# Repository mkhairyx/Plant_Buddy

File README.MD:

# Plant Buddy

## The reason I made it
I have a plant at a remote location and I only go there once in a while, I was afraid that that plant might die because of the lack of water so I decided to make this device. It work by connecting a water pump to it, then it drives this pump every 20 days by default (configurable in the code). It measures the soil humidity for feedback to the user (which is delivered through SMS).

## The poster

## Photos

|Schematic                                            |PCB                                    |3D View                                  |Showcase                                            |
|-----------------------------------------------------|---------------------------------------|-----------------------------------------|----------------------------------------------------|
|||||

## Step files
All of the step files can be found [here](./Step_Files/).
<br>

## Firmware
### Compile and flash using the Arduino IDE
If you want to edit the code, compile it yourself, then flash it; you can download the arduino sketch [here](./Source/Firmware/Arduino/plant_buddy).

### Flash the firmware as is
If you want to flash the firmware as is, you can download it [here](./source/Firmware/Firmware). <br>
You can use [ESPWebTool](https://esptool.spacehuhn.com) to flash the firmware directly to the ESP32 using your browser.<br>
Note that there might be some changes between the Arduino code and the firmware as some changes were made.

## Device Operation
### Power supply
The device is powered a 3.7V recharge Li-Po battery.<br>
The battery is recharged daily using a 3W 6V mini solar panel connected to a mini solar charger which is connected to a buck converter to operate the ESP32.<br>
The ESP32 goes into Deep Sleep mode in between watering sessions to help decrease energy consumption.<br>

### Startup Notification

Whenever the ESP32 wakes up, it sends a status report to the user containing:

* Current battery level
* Current soil moisture level
* Watering interval
* Reason for waking up

Example:

```
The device just booted up!
Battery level: 87%
Soil humidity: 42%
Watering interval: 3 days

Boot reason: Watering cycle completed successfully.
Watering again in 3 days.
```

Possible boot reasons:

| Boot Reason              | Description                                                                       |
| ------------------------ | --------------------------------------------------------------------------------- |
| Unknown Fault            | The device restarted unexpectedly due to an unknown error.                        |
| Watering Cycle Completed | A watering cycle has just finished successfully, and a new countdown has started. |
| First Boot               | The device has been powered on for the first time.                                |

## BOM
### BOM Table (components only)
|Name                                                 |Link                                   |Cost per one (EGP)                       |Cost per one (USD)                                  |Amount     |Total cost|
|-----------------------------------------------------|---------------------------------------|-----------------------------------------|----------------------------------------------------|-----------|----------|
|JST Connectors                                       |https://www.ram-e-shop.com/shop/pw-m-pcb-2pin-pw-m-2-pin-polarized-male-jst-xh2-54-connector-for-pcb-6463| EGP 0.60                                | $0.012                                             |5          | $0.060   |
|4.7uF Caps (1206)                                    |https://lampatronics.com/product/smd-multilayer-ceramic-capacitor-1206-4-7uf-16v-1pcs| EGP 1.50                                | $0.030                                             |4          | $0.120   |
|100nF Caps (0805)                                    |https://lampatronics.com/product/smd-multilayer-ceramic-capacitor-0805-2012-104-100nf-50v-1pcs-2| EGP 1.00                                | $0.020                                             |6          | $0.120   |
|1uF Caps (0805)                                      |https://lampatronics.com/product/smd-ceramic-capacitor-0805-1051uf-50v-1pcs| EGP 1.50                                | $0.030                                             |1          | $0.030   |
|10uF Caps (0805)                                     |https://lampatronics.com/product/smd-multilayer-ceramic-capacitor-0805-10610uf-16v-1pcs| EGP 1.50                                | $0.030                                             |1          | $0.030   |
|1N4148WS Diode                                       |https://lampatronics.com/product/smd-diode-1n4148ws-10pcs| EGP 7.50                                | $0.150                                             |1          | $0.150   |
|Screw terminal                                       |https://www.ram-e-shop.com/shop/r-3-roseta-2pin-2-pin-pcb-screw-terminal-block-pitch-5mm-r-3-5854| EGP 3.00                                | $0.060                                             |1          | $0.060   |
|Male headers                                         |https://store.fut-electronics.com/products/male-pin-headers-standard-2-54-mm-40-pin?_pos=1&_sid=73894fcce&_ss=r| EGP 10.00                               | $0.200                                             |1          | $0.200   |
|Female headers                                       |https://www.ram-e-shop.com/shop/ph35-1x4-female-ph35-pin-header-female-1x4-straight-2-54mm-6976| EGP 1.50                                | $0.030                                             |2          | $0.060   |
|AO3401 (transistor for pump)                         |https://uge-one.com/product/ao3401-sot23-general-purpose-p-channel-mosfet-smd-transistor-sot-23/| EGP 3.00                                | $0.060                                             |1          | $0.060   |
|1K ohm Resistors                                     |https://lampatronics.com/product/smd-resistor-1kohm-102-0805-10pcs| EGP 2.00                                | $0.040                                             |1          | $0.040   |
|1M ohm Resistors                                     |https://lampatronics.com/product/smd-resistor-1mohm-105-0805-10pcs| EGP 2.00                                | $0.040                                             |1          | $0.040   |
|10K ohm Resistors                                    |https://lampatronics.com/product/smd-resistor-10kohm-103-0805-10pcs| EGP 2.00                                | $0.040                                             |1          | $0.040   |
|330 ohm Resistors                                    |https://lampatronics.com/product/smd-resistor-330ohm-331-0805-10pcs| EGP 2.00                                | $0.040                                             |1          | $0.040   |
|1.5Kohm Resistors                                    |https://lampatronics.com/product/resistor-1-5k-ohm-1-4w-4pcs-2| EGP 0.30                                | $0.006                                             |1          | $0.006   |
|2K ohm Resistors                                     |https://lampatronics.com/product/smd-resistor-2kohm-202-0805-10pcs| EGP 2.00                                | $0.040                                             |1          | $0.040   |
|3K ohm Resistors                                     |https://lampatronics.com/product/smd-resistor-3kohm-302-0805-10pcs| EGP 2.00                                | $0.040                                             |1          | $0.040   |
|220 ohm Resistors                                    |https://lampatronics.com/product/smd-resistor-220ohm-221-0805-10pcs| EGP 2.00                                | $0.040                                             |1          | $0.040   |
|Reset Push Button                                    |https://lampatronics.com/product/push-button-4pin-long-6x6x13mm| EGP 1.50                                | $0.030                                             |1          | $0.030   |
|Voltage Regulator                                    |https://lampatronics.com/product/ams1117-33v-sot-223-33v-linear-voltage-regulator| EGP 2.00                                | $0.040                                             |1          | $0.040   |
|TLC555xD (Capacitive soil readings)                  |https://uge-one.com/product/tlc555cdr-low-power-cmos-timer-ic-smd-sop8/| EGP 35.00                               | $0.700                                             |1          | $0.700   |
|PC817 optocoupler                                    |https://lampatronics.com/product/pc817-optocoupler-dip-4| EGP 1.25                                | $0.025                                             |1          | $0.025   |
|ESP32 DevKit                                         |https://lampatronics.com/product/esp32-30pin-development-board-wifi-and-bluetooth| EGP 325.00                              | $6.500                                             |1          | $6.500   |
|Water Pump                                           |https://www.ram-e-shop.com/shop/dc-pump-6vdc-water-pump-3-6vdc-mini-120l-h-7422| EGP 45.00                               | $0.900                                             |1          | $0.900   |
|Hose (inner d: 6mm , outer d: 8mm) 1 Meter           |https://lampatronics.com/product/flexible-clear-hose-tube-pipe-6mm-airwater-pump-pvc| EGP 15.00                               | $0.300                                             |2          | $0.600   |
|Water Flow sensor                                    |https://store.fut-electronics.com/products/water-flow-rate-sensor?_pos=8&_sid=5e9c09df8&_ss=r| EGP 260.00                              | $5.200                                             |1          | $5.200   |
|SIM800L GSM Module                                   |https://store.fut-electronics.com/collections/gsm-gprs/products/sim800l-gprs-gsm-module-esp-core-board-with-built-in-antenna| EGP 280.00                              | $5.600                                             |1          | $5.600   |
|3W 6V Mini Solar Panel                               |https://store.fut-electronics.com/products/solar-cell-129-x-129-mm-3w?_pos=3&_sid=fdb2b11fe&_ss=r| EGP 155.00                              | $3.100                                             |1          | $3.100   |
|Mini solar charger                                   |https://store.fut-electronics.com/products/solar-usb-charger-for-lithium-batteries-lipo-rider?_pos=5&_sid=fdb2b11fe&_ss=r| EGP 160.00                              | $3.200                                             |1          | $3.200   |
|Battery                                              |https://store.fut-electronics.com/products/3-7v-rechargeable-polymer-lithium-ion-battery-ecocell?_pos=3&_sid=4fcef8d7d&_ss=r| EGP 125.00                              | $2.500                                             |1          | $2.500   |
|M5 Screws                                            |https://store.fut-electronics.com/products/screw-m5x25mm-hexagonal-head?_pos=5&_sid=c4191184f&_ss=r| EGP 2.00                                | $0.040                                             |4          | $0.160   |
|                                                     |                                       |                                         |                                                    |           |          |
|                                                     |                                       |                                         |                                                    |Whole Total| $29.731  |

### Quotes
[JLCPCB](https://jlcpcb.com) : $57.12

<br>
Note that local manufacturers might have different prices.

## Notes
A future V2 is planned with support for multiple probes, improved power efficiency, and user-requested status updates.

> Made and designed by [@mkhairyx](https://github.com/mkhairyx).<br>
Supported by [Fallout](https://fallout.hackclub.com/) and [Hack Club](https://hackclub.com).<br>

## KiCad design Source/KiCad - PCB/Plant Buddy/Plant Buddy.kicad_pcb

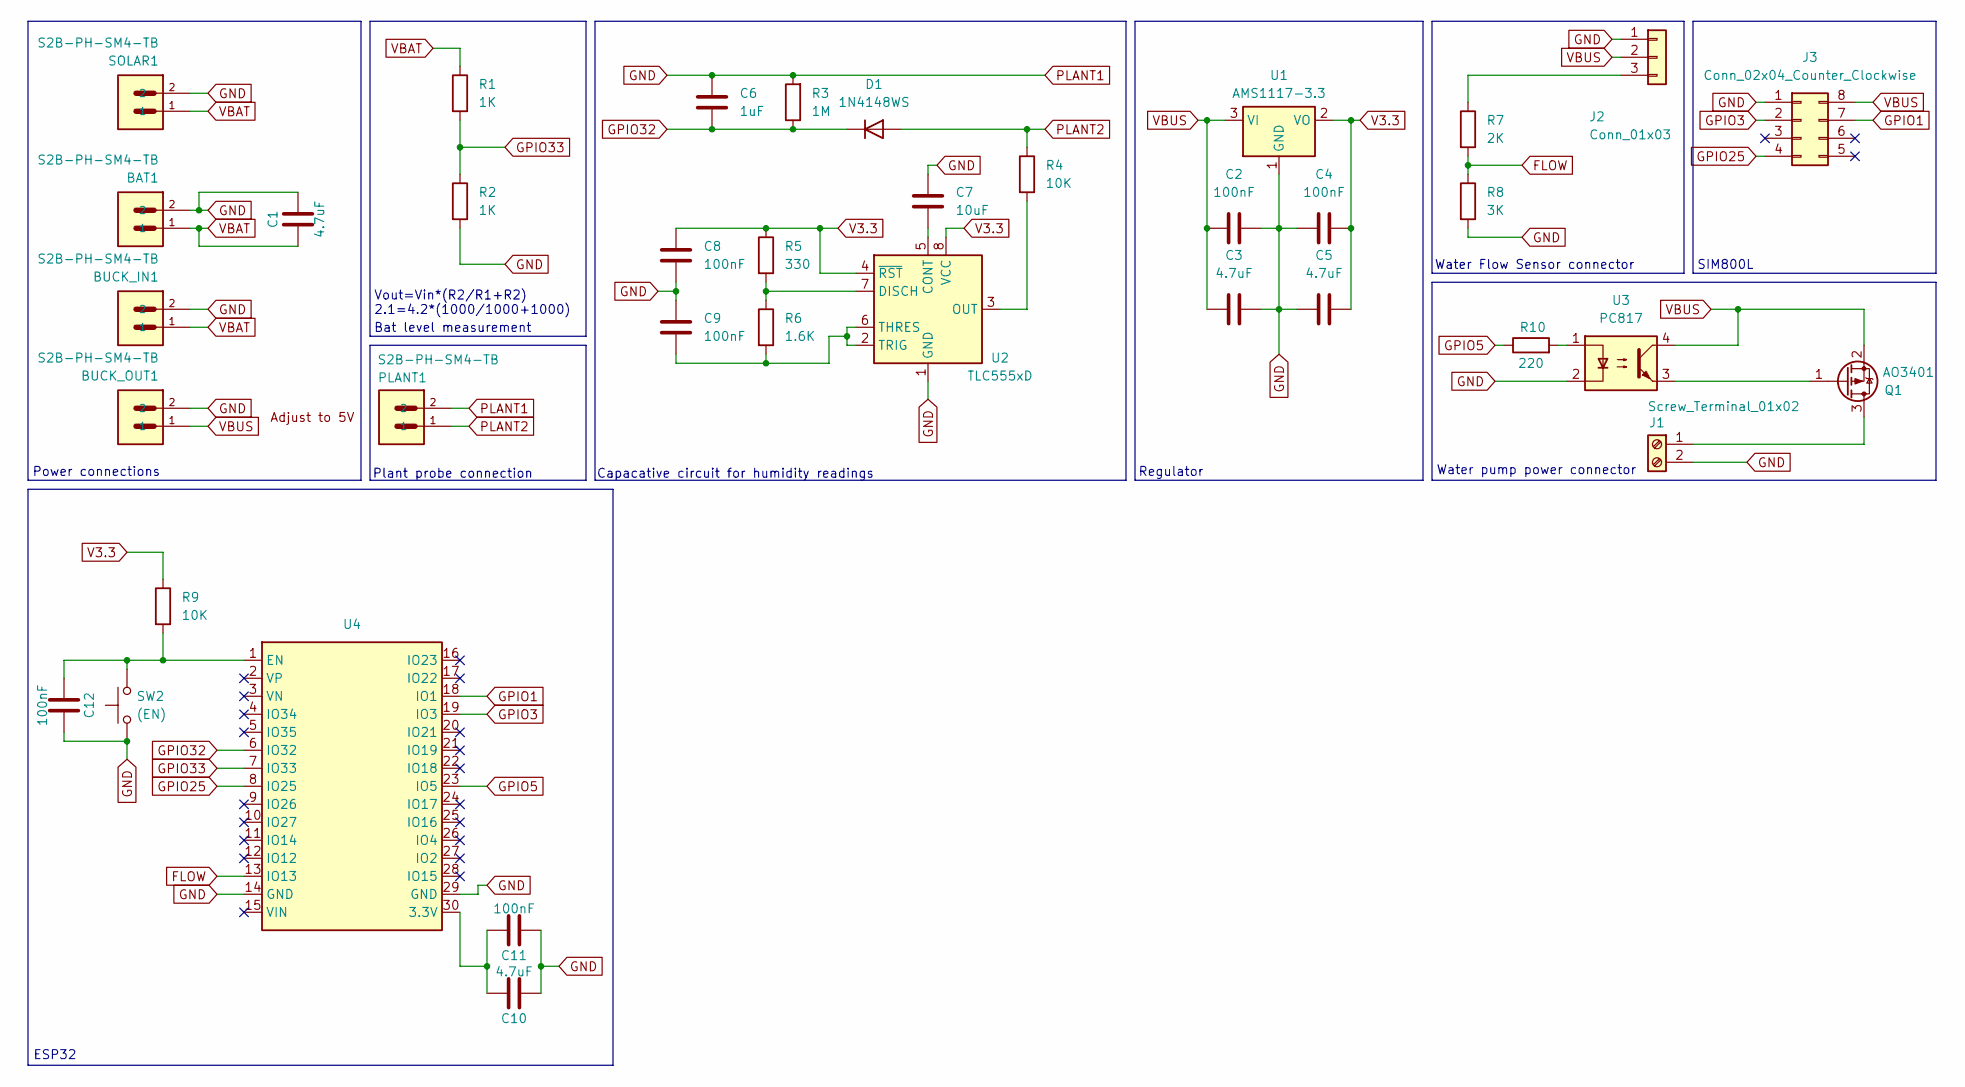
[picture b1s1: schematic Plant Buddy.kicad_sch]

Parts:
BAT1: S2B-PH-SM4-TB; JST_EH_B2B-EH-A_1x02_P2.50mm_Vertical
BUCK_IN1: S2B-PH-SM4-TB; JST_EH_B2B-EH-A_1x02_P2.50mm_Vertical
BUCK_OUT1: S2B-PH-SM4-TB; JST_EH_B2B-EH-A_1x02_P2.50mm_Vertical
C1, C3, C5, C10: 4.7uF; C_1206_3216Metric_Pad1.33x1.80mm_HandSolder
C2, C4, C8, C9: 100nF; C_0805_2012Metric_Pad1.18x1.45mm_HandSolder
C6: 1uF; C_0805_2012Metric_Pad1.18x1.45mm_HandSolder
C7: 10uF; C_0805_2012Metric_Pad1.18x1.45mm_HandSolder
C11, C12: 100nF; C_1206_3216Metric_Pad1.33x1.80mm_HandSolder
D1: 1N4148WS; D_SOD-323_HandSoldering
J1: Screw_Terminal_01x02; Altech_AK100_1x02_P5.00mm
J2: Conn_01x03; PinSocket_1x03_P2.54mm_Vertical
J3: Conn_02x04_Counter_Clockwise; PinSocket_2x04_P2.54mm_Vertical
PLANT1: S2B-PH-SM4-TB; JST_EH_B2B-EH-A_1x02_P2.50mm_Vertical
Q1: AO3401; SOT-23
R1, R2: 1K; R_0805_2012Metric_Pad1.20x1.40mm_HandSolder
R3: 1M; R_0805_2012Metric_Pad1.20x1.40mm_HandSolder
R4, R9: 10K; R_0805_2012Metric_Pad1.20x1.40mm_HandSolder
R5: 330; R_0805_2012Metric_Pad1.20x1.40mm_HandSolder
R6: 1.6K; R_Axial_DIN0207_L6.3mm_D2.5mm_P7.62mm_Horizontal
R7: 2K; R_0805_2012Metric_Pad1.20x1.40mm_HandSolder
R8: 3K; R_0805_2012Metric_Pad1.20x1.40mm_HandSolder
R10: 220; R_0805_2012Metric_Pad1.20x1.40mm_HandSolder
SOLAR1: S2B-PH-SM4-TB; JST_EH_B2B-EH-A_1x02_P2.50mm_Vertical
SW2: (EN); SW_PUSH_6mm_H13mm
U1: AMS1117-3.3; SOT-223-3_TabPin2
U2: TLC555xD; SOP-8_3.76x4.96mm_P1.27mm
U3: PC817; DIP-4_W7.62mm
U4: ESP32 DevKit

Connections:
FLOW: R7.2, R8.1, U4.13 (IO13)
GND: BAT1.2, BUCK_IN1.2, BUCK_OUT1.2, C1.2, C2.2, C3.2, C4.2, C5.1, C6.2, C7.1, C8.1, C9.1, C10.1, C11.1, C12.2, J1.2, J2.1, J3.1, PLANT1.2, R2.2, R3.2, R8.2, SOLAR1.2, SW2.1, U1.1 (GND), U2.1 (GND), U3.2, U4.14 (GND), U4.29 (GND)
GPIO1: J3.7, U4.18 (IO1)
GPIO3: J3.2, U4.19 (IO3)
GPIO5: R10.1, U4.23 (IO5)
GPIO25: J3.4, U4.8 (IO25)
GPIO32: C6.1, D1.1 (K), R3.1, U4.6 (IO32)
GPIO33: R1.2, R2.1, U4.7 (IO33)
unnamed: J1.1, Q1.3 (D)
unnamed: J2.3, R7.1
unnamed: Q1.1 (G), U3.3
unnamed: R10.2, U3.1
unnamed: C7.2, U2.5 (CONT)
unnamed: R5.2, R6.1, U2.7 (DISCH)
unnamed: R4.2, U2.3 (OUT)
unnamed: C9.2, R6.2, U2.2 (TRIG), U2.6 (THRES)
unnamed: C10.2, C11.2, U4.30 (3.3V)
unnamed: C12.1, R9.2, SW2.2, U4.1 (EN)
PLANT2: D1.2 (A), PLANT1.1, R4.1
V3.3: C4.1, C5.2, C8.2, R5.1, R9.1, U1.2 (VO), U2.4 (~RST), U2.8 (VCC)
VBAT: BAT1.1, BUCK_IN1.1, C1.1, R1.1, SOLAR1.1
VBUS: BUCK_OUT1.1, C2.1, C3.1, J2.2, J3.8, Q1.2 (S), U1.3 (VI), U3.4

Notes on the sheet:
ESP32
Vout=Vin*(R2/R1+R2) 2.1=4.2*(1000/1000+1000)
Water pump power connector
SIM800L
Water Flow Sensor connector
Capacative circuit for humidity readings
Regulator
Plant probe connection
Bat level measurement
Power connections

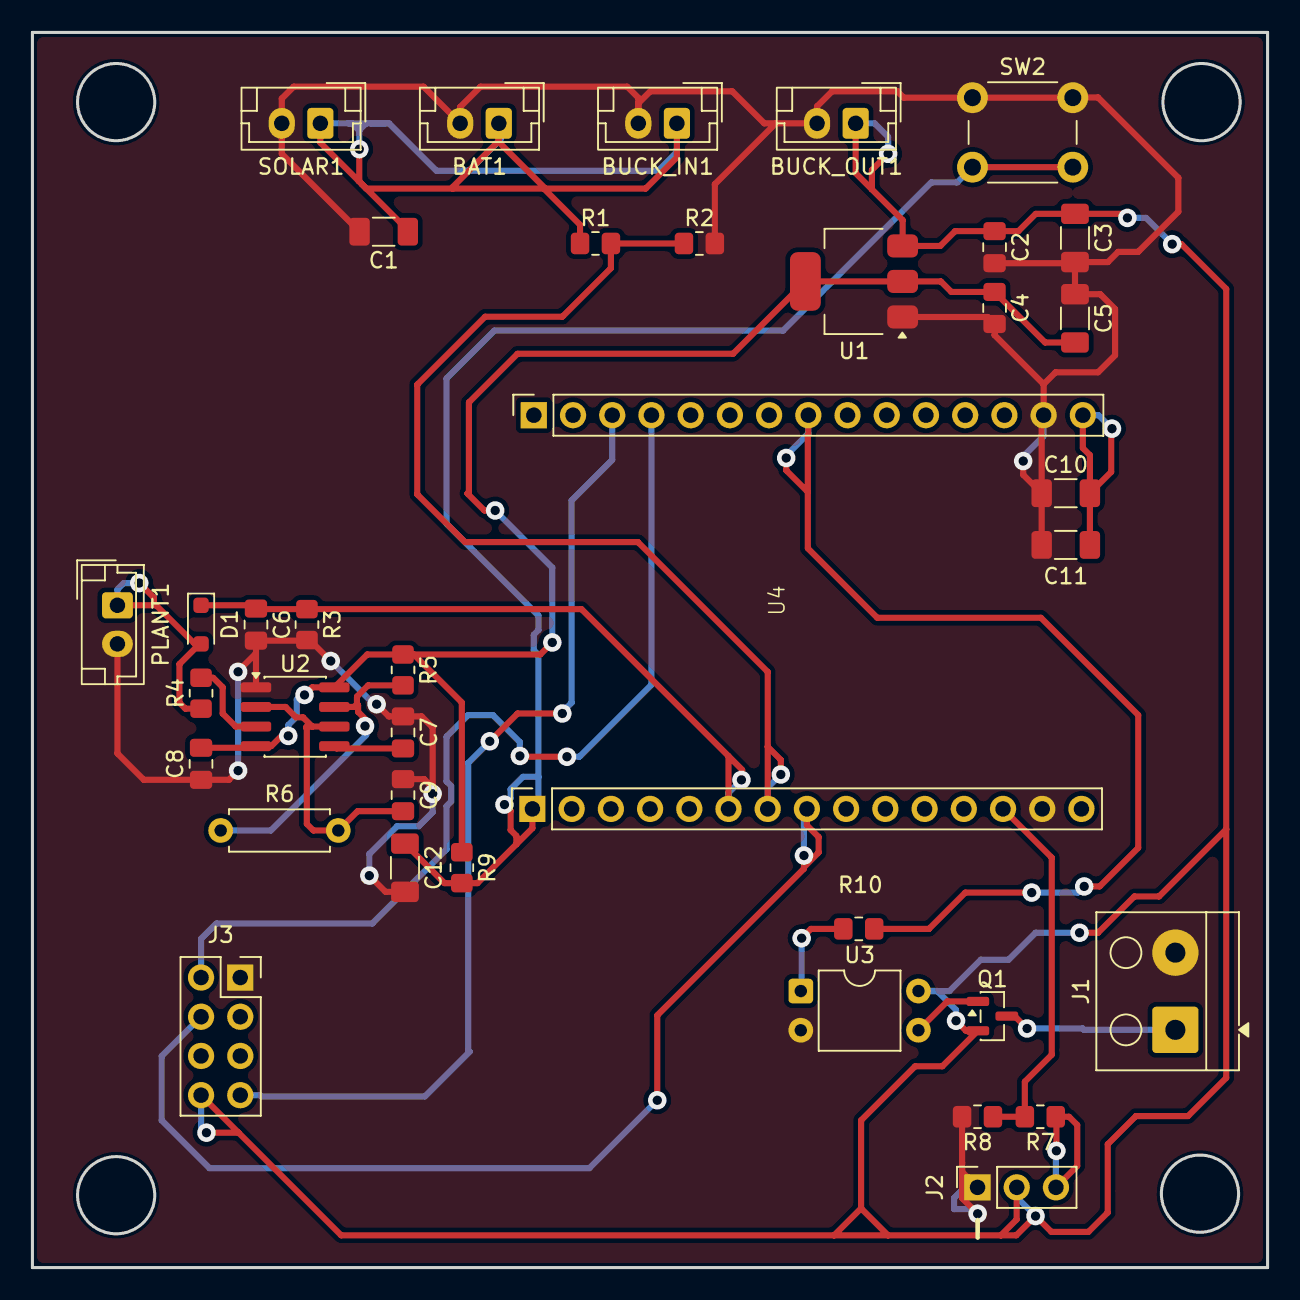
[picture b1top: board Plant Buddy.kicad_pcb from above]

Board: 2 copper layers, 80.0 x 80.0 mm, 37 parts (0 on the bottom side), 22 nets.

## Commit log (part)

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2026-06-17 Added KiCad files
2026-06-17 Added water flow sensor connector
2026-06-17 Kicad saved
2026-06-18 Finished Schematic and PCB
2026-06-19 Edited PCB and schematics.
2026-06-20 Finished the firmware and modified the schematics and the PCB
2026-06-20 Firmware uploaded
2026-06-20 Designed 3D case
2026-06-21 First render done.
2026-06-21 Edited textures
2026-06-21 Uploaded Media
2026-06-21 Added more project files
2026-06-22 Added BOM
    Added the BOM, and modified the schematics to have a resistor that I can buy.
2026-06-24 Added the zine poster
2026-06-25 Removed firmware from the Arduino folder
2026-06-25 README, BOM, Code were changed
    Added a README, changed the BOM with the correct info, modified the code to print % next to the battery percentage, and added a picture of a quote from JLCPCB
2026-06-25 Fix README description
